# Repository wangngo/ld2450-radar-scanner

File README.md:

# ESP32-S3 + HLK-LD2450 24GHz mmWave Handheld Radar Scanner (with BMI160 Gyro Shake Compensation)

> **Handheld 24GHz mmWave multi-target human radar scanner** powered by **Hi-Link HLK-LD2450** (up to 3 simultaneous targets, 6m range, ±60° azimuth), **ESP32-S3-DevKitC-1 (N16R8)**, **Bosch BMI160 6-axis IMU** for handheld motion/shake compensation, and **on-board WS2812 RGB LED** proximity alerts.
>
> Features a zero-dependency **Wi-Fi SoftAP Web Radar UI** (`http://192.168.4.1` at ~11Hz live update), WebAudio distance-scaled Geiger beep, EMA trajectory smoothing, ghost-on-loss tracking, CSV data logging, **17 native C++ unit tests**, interactive HTML wiring/perfboard guides, and programmatic **KiCad 10 Schematic (`ERC 0`) & Carrier PCB (`DRC 0/0` + JLCPCB Gerbers)**.

---

## 1. Key Engineering Highlights

### A. Custom Stream-Safe `ld2450_parser` (Fixes 3 Bugs in Existing Libraries & Official Manual)

Why we wrote [`lib/ld2450_parser`](lib/ld2450_parser) instead of using popular Arduino libraries such as `RBEGamer/HLK-LD2450`:
1. **Fixes Out-of-Bounds (OOB) Memory Read:** Existing libraries check the frame footer at `rec_buf[i+28]` / `rec_buf[i+29]` without verifying `i + 29 < len`, causing out-of-bounds reads past the 256-byte receive buffer.
2. **Resilient to Split UART Frames at `256000` Baud:** Instead of relying on `Serial.readBytes()` with a 10ms timeout (which drops frames split across two reads), `Ld2450Parser` is a byte-by-byte streaming state machine that resynchronizes seamlessly on header (`AA FF 03 00`) and footer (`55 CC`).
3. **Correct Euclidean Distance vs. Distance-Gate Resolution (+ Official Manual Errata):**
   - Each 8-byte target record contains `(x_mm, y_mm, speed_cm_s, resolution_mm)`.
   - Existing libraries erroneously assign `target.distance = resolution`. In reality, the 4th field is the radar's *distance-gate resolution* (`320 mm`), while true distance is $\sqrt{x^2 + y^2}$ (`hypot(x_mm, y_mm)`).
   - **Official Manual Errata:** Hi-Link's `HLK-LD2450 Manual V1.00` (`docs/datasheets/HLK-LD2450-manual-V1.00.pdf`) contains an arithmetic typo in its worked example, writing `0x40 + 0x01*256 = 360 mm` when `0x0140` is actually **`320 mm`**.
4. **Boot-Time Multi-Target Configuration State Machine (`ld2450_cmd.h`):**
   - Automatically runs the Hi-Link binary command sequence on startup: `0x00FF` (Enable Config) → `0x0091` (Query Target Mode) → `0x0090` (Switch to Multi-Target if in Single mode) → `0x00FE` (End Config), with automatic retry if the radar stays silent in config mode.

### B. Handheld Motion & Shake Compensation (`lib/shake_detect` + Bosch `BMI160`)

Doppler 24GHz mmWave radars measure relative radial velocity. When a handheld scanner is tilted or panned by the operator's hand, stationary walls and objects appear as false moving targets, and the radar's rear lobe can pick up the operator behind the antenna:
- **Physical Shielding:** A metal backplate behind the LD2450 blocks rear-lobe reflections toward the operator (see cross-section in [`docs/wiring.html`](docs/wiring.html)).
- **100Hz Gyro Hysteresis Filter (`lib/shake_detect`):** Reads angular velocity magnitude $\|\omega\| = \sqrt{\omega_x^2 + \omega_y^2 + \omega_z^2}$ at 100Hz (`±250 °/s`) via the official Bosch Sensortec BMI160 driver (`lib/bmi160`, BSD-3-Clause).
  - Trips **ON** when $\|\omega\| \ge 30\text{ °/s}$, holds while $\ge 15\text{ °/s}$, and clears after **`300 ms`** of steady hold.
  - While shaking is detected, the Web UI dims radar targets and displays a shake warning banner, the CSV logger flags `shake=1`, and the on-board WS2812 RGB LED switches to dim blue instead of firing false proximity alerts.

### C. Hardware-as-Code: Programmatic KiCad 10 Schematic, PCB & Netlist-Verified Perfboard

All hardware design artifacts are generated and cross-checked deterministically via Python scripts in [`hardware/`](hardware):
- **`hardware/gen_schematic.py`** → [`hardware/carrier/carrier.kicad_sch`](hardware/carrier/carrier.kicad_sch) (**KiCad 10 ERC: 0 errors**) & [`carrier-schematic.pdf`](hardware/carrier/carrier-schematic.pdf).
- **`hardware/gen_carrier.py`** → [`hardware/carrier/carrier.kicad_pcb`](hardware/carrier/carrier.kicad_pcb) (66×66mm 2-layer Carrier PCB with top antenna notch, **KiCad 10 DRC: 0 violations, 0 unconnected**) & ready-to-order JLCPCB bundle [`carrier-gerber.zip`](hardware/carrier/carrier-gerber.zip).
- **`hardware/gen_perfboard.py`** → [`docs/perfboard.html`](docs/perfboard.html) (top & mirrored bottom soldering guide for a standard 7×9cm 24×30-hole perfboard, **automatically verified against the KiCad schematic netlist**).

---

## 2. Verified Pinout (`ESP32-S3-DevKitC-1 N16R8`)

> Interactive visual wiring diagram: open [`docs/wiring.html`](docs/wiring.html) and [`docs/perfboard.html`](docs/perfboard.html) in any browser.

| Peripheral | Module Pin | ESP32-S3 Pin | Notes & Hardware Gotchas |
| :--- | :--- | :--- | :--- |
| **HLK-LD2450** *(UART1 @ 256000)* | `5V` | `5V` | Requires **>200mA** at 5V (3.3V IO level). |
| | `GND` | `GND` | Common ground. |
| | `TX` | **`GPIO18`** *(RX1)* | Cross-over TX → RX. Avoid GPIO43/44 (used by onboard USB-UART0) and GPIO33–37 (used by Octal PSRAM on N16R8). |
| | `RX` | **`GPIO17`** *(TX1)* | Cross-over RX ← TX. |
| **Bosch BMI160** *(CJMCU-160, I2C @ 400kHz)* | `VIN` | `3V3` | Power from 3.3V rail. |
| | `GND` | `GND` | Common ground. |
| | `SDA` | **`GPIO8`** | I2C Data. |
| | `SCL` | **`GPIO9`** | I2C Clock. |
| | `CS` | **`3V3`** | **Must tie to `3V3`** to select I2C mode (`CS` low selects SPI). |
| | `SAO` *(SDO)* | **`GND`** | **Must tie to `GND`** for I2C address `0x68` (if left floating, module pull-up shifts address to `0x69`). |
| **On-Board RGB LED** | `WS2812` | **`GPIO48`** | Distance alert: Green (>4m) → Yellow → Flashing Red (faster as target approaches <4m); Dim Blue when shaking. |

---

## 3. Building, Testing & Flashing (PlatformIO)

### Run the 17 Native Unit Tests (No Hardware Required)
Tests cover `ld2450_parser` (datasheet frames, garbage resync, split frames, bad footer, 3-target decoding), `ld2450_cmd` / `ld2450_filter` (range gating, `y <= 0` behind-antenna rejection, optional `<1m` clustering), and `shake_detect` hysteresis:

```bash
pio test -e native
```

### Build & Flash Firmware (`s3_web`)
```bash
pio run -e s3_web -t upload
```
1. On your phone or laptop, connect to Wi-Fi AP **`LD2450-Radar`** (password: **`radar2450`**).
2. Open **`http://192.168.4.1`** in your browser.

### Hardware Bring-Up & Diagnostic Environments (`platformio.ini`)
- **`pio run -e s3_log -t upload`**: Identical to `s3_web` but with `ARDUINO_USB_CDC_ON_BOOT=0` so boot logs (`# radar cfg xong`, `# bmi160 chip 0xD1 ok`) output over the `CH340` UART0 USB port instead of the native USB CDC port.
- **`pio run -e i2cscan -t upload`**: Scans I2C bus on `GPIO8/9` and reads register `0x00` (`chip_id = 0xD1`) at `0x68` and `0x69` (`diag/i2cscan.cpp`).
- **`pio run -e led_test -t upload`**: Alternates `GPIO48` (Red) and `GPIO38` (Blue) to identify the on-board WS2812 pin across DevKitC-1 v1.0 / v1.1 revisions (`diag/led_test.cpp`).

---

## 4. Repository Structure

```text
├── src/
│   ├── main.cpp            # Firmware entry, Wi-Fi AP, HTTP endpoints (/data, /cfg), boot cfg FSM
│   ├── web_page.h          # Embedded HTML5 Canvas radar UI + WebAudio Geiger beep + CSV export
│   ├── imu.h               # Bosch BMI160 I2C wrapper (100Hz gyro -> shake_detect)
│   └── led.h               # WS2812 RGB LED distance & shake indicator
├── lib/
│   ├── ld2450_parser/      # Stream-safe LD2450 frame parser, Hi-Link command builder & target filters
│   ├── shake_detect/       # Gyro angular-velocity hysteresis detector
│   └── bmi160/             # Official Bosch Sensortec BMI160 driver (BSD-3-Clause)
├── test/                   # 17 native Unity unit tests (test_parser, test_cmd_filter, test_shake)
├── diag/                   # Hardware bring-up tools (i2cscan.cpp, led_test.cpp)
├── hardware/               # Python generators + KiCad 10 Schematic (ERC 0), PCB (DRC 0/0) & Gerbers
└── docs/                   # Interactive HTML wiring (wiring.html), 7x9cm perfboard guide (perfboard.html) & datasheet
```

---

## Tóm tắt Tiếng Việt

Dự án **Máy quét Radar cầm tay 24GHz mmWave (`HLK-LD2450` + `ESP32-S3-DevKitC-1 N16R8` + Gyro `Bosch BMI160` + LED RGB `WS2812`)**:
1. **Thư viện `lib/ld2450_parser` tự viết (17/17 test native PASS):** Sửa 3 lỗi của thư viện `RBEGamer/HLK-LD2450` (đọc tràn bộ nhớ OOB, mất gói UART bị cắt ở 256000 baud, gán nhầm độ phân giải 320mm thành khoảng cách `hypot(x,y)`) và đính chính lỗi cộng nhầm `360mm` vs `320mm` trong manual Hi-Link V1.00; tự động cấu hình chế độ multi-target (`0x00FF` → `0x0091` → `0x0090` → `0x00FE`) lúc khởi động.
2. **Chống nhiễu khi tay cầm rung (`BMI160` + `shake_detect`):** Đọc tốc độ góc gyro 100Hz, tự động làm mờ mục tiêu nhiễu trên giao diện Web (`http://192.168.4.1`) và báo LED xanh dương khi lia/lắc máy. Lưu ý phần cứng module CJMCU-160: phải nối **`CS → 3V3`** (chọn I2C) và **`SAO → GND`** (giữ địa chỉ `0x68`, nếu để hở chân `SAO` bị kéo lên `0x69`).
3. **Phần cứng & Mạch in:** Mở [`docs/wiring.html`](docs/wiring.html) và [`docs/perfboard.html`](docs/perfboard.html) để xem sơ đồ đấu nối trực quan và hướng dẫn hàn board đục lỗ 7×9cm (đã tự động đối chiếu netlist với KiCad 10 Schematic & Carrier PCB Gerber trong [`hardware/carrier/`](hardware/carrier)).

---

## License

MIT License (see [`LICENSE`](LICENSE)). `lib/bmi160/` is licensed under the BSD-3-Clause License by Bosch Sensortec.

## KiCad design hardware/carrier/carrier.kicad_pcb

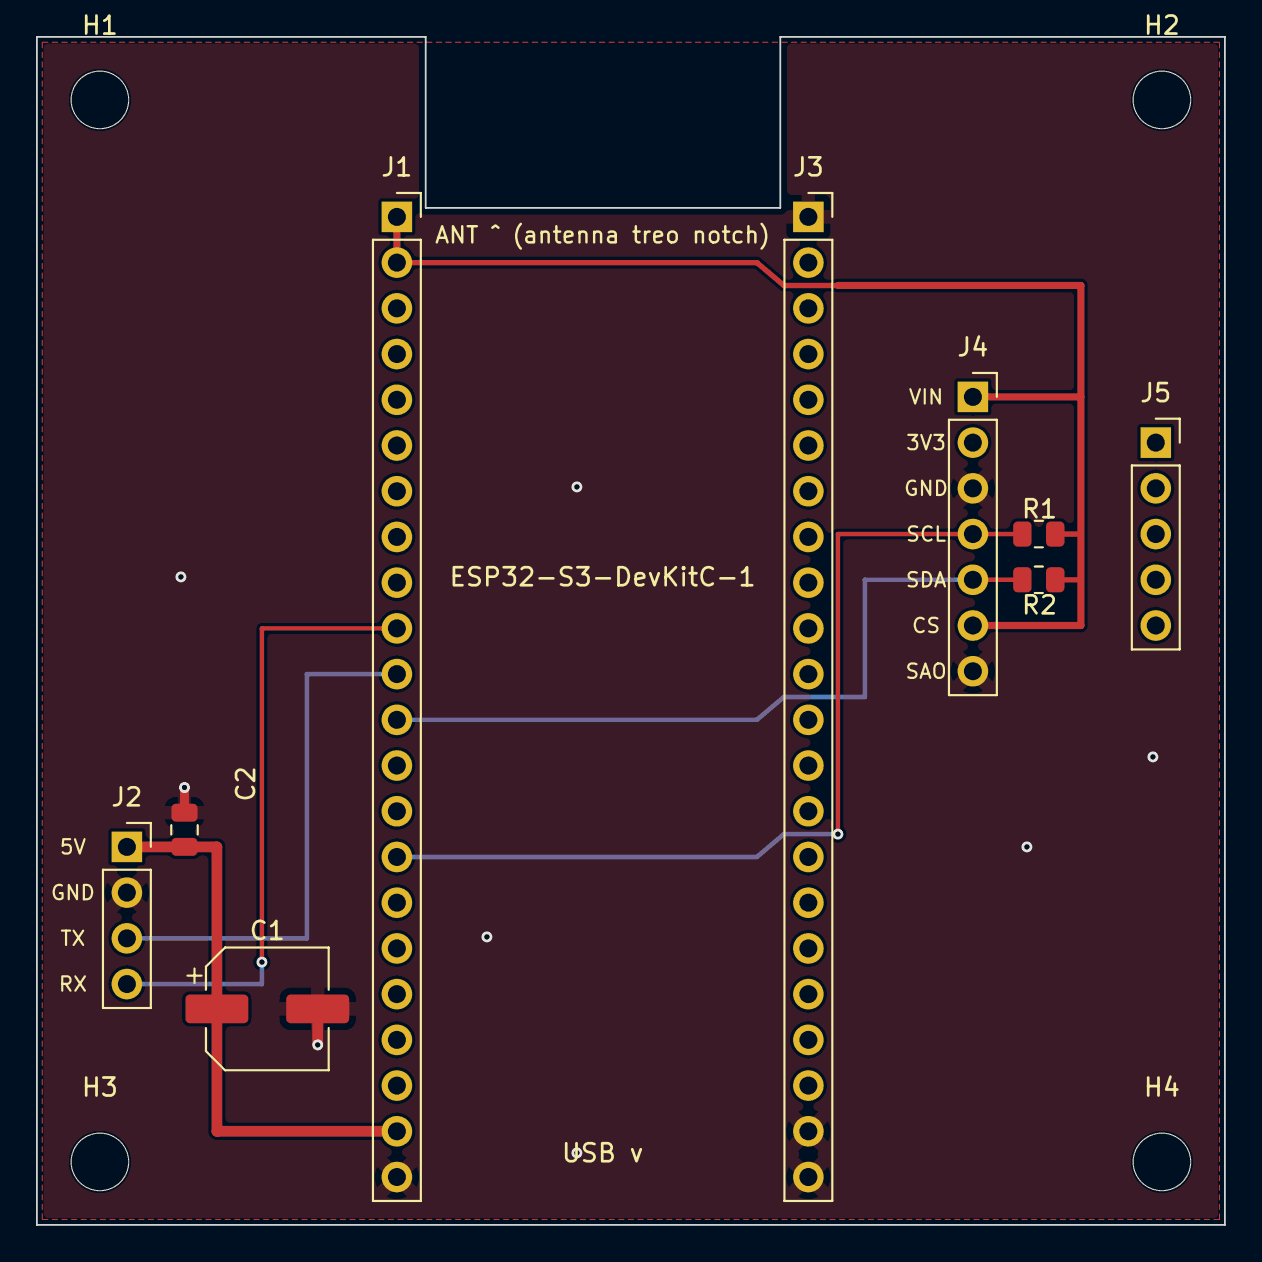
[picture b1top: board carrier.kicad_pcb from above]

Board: 2 copper layers, 66.0 x 66.0 mm, 13 parts (0 on the bottom side), 7 nets.

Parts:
C1: 100uF/10V; CP_Elec_6.3x5.4
C2: 100nF; C_0805_2012Metric
H1, H2, H3, H4: M3; MountingHole_3.2mm_M3
J1: DevKitC_J1; PinSocket_1x22_P2.54mm_Vertical
J2: LD2450; PinSocket_1x04_P2.54mm_Vertical
J3: DevKitC_J3; PinSocket_1x22_P2.54mm_Vertical
J4: BMI160_R; PinSocket_1x07_P2.54mm_Vertical
J5: BMI160_L; PinSocket_1x05_P2.54mm_Vertical
R1, R2: 4k7 DNP; R_0805_2012Metric

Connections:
+3V3: J1.1, J1.2, J4.1, J4.6, R1.2, R2.2
+5V: C1.1, C2.1, J1.21, J2.1
GND: C1.2, C2.2, J1.22, J2.2, J3.1, J3.21, J3.22, J4.3, J4.7
I2C_SCL: J1.15, J4.4, R1.1
I2C_SDA: J1.12, J4.5, R2.1
UART_RX: J1.11, J2.3
UART_TX: J1.10, J2.4

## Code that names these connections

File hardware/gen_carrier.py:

"""Sinh PCB carrier (ESP32-S3-DevKitC-1 + LD2450 + BMI160) bằng pcbnew của KiCad 10.

Chạy bằng Python đi kèm KiCad:
  /Applications/KiCad/KiCad.app/Contents/Frameworks/Python.framework/Versions/Current/bin/python3 hardware/gen_carrier.py
Netlist = docs/kicad-prep.md. Toạ độ mm, gốc góc trên-trái board, y hướng xuống.
Nguồn kích thước:
  - DevKitC-1 v1.1: DXF Espressif 20220429 -> pitch 2.54, J1 x=1.27 / J3 x=24.13 => row-to-row 22.86mm,
    chân 1 phía antenna, USB phía chân 22. Pinout J1/J3 theo user guide v1.1.
  - BMI160 CJMCU-160: 1x7 + 1x5, cách 10.16mm, hàng 5 lệch 1 bước (nằm giữa) — W xác nhận 2026-11-06.
  - LD2450: 1x4 5V/GND/Tx/Rx theo manual HLK V1.00 (chưa soi module thật).
"""
import os
import pcbnew

HERE = os.path.dirname(os.path.abspath(__file__))
OUT = os.path.join(HERE, "carrier", "carrier.kicad_pcb")
FPLIB = "/Applications/KiCad/KiCad.app/Contents/SharedSupport/footprints"
P = 2.54

B = pcbnew.BOARD()
mm = pcbnew.FromMM
V = lambda x, y: pcbnew.VECTOR2I(mm(x), mm(y))

ds = B.GetDesignSettings()
ds.m_TrackMinWidth = mm(0.2)
ds.m_ViasMinSize = mm(0.6)
ds.m_MinClearance = mm(0.2)

NETS = {}
def net(name):
    if name not in NETS:
        n = pcbnew.NETINFO_ITEM(B, name)
        B.Add(n)
        NETS[name] = n
    return NETS[name]

def fp(lib, name, ref, value, x, y, rot=0, pinnets=None):
    f = pcbnew.FootprintLoad(os.path.join(FPLIB, lib + ".pretty"), name)
    f.SetReference(ref)
    f.SetValue(value)
    f.SetPosition(V(x, y))
    if rot:
        f.SetOrientationDegrees(rot)
    B.Add(f)
    for pad in f.Pads():
        n = (pinnets or {}).get(pad.GetNumber())
        if n:
            pad.SetNet(net(n))
    return f

def pad_xy(f, num):
    p = [p for p in f.Pads() if p.GetNumber() == str(num)][0].GetPosition()
    return pcbnew.ToMM(p.x), pcbnew.ToMM(p.y)

def track(netname, pts, w, layer=pcbnew.F_Cu):
    for (x1, y1), (x2, y2) in zip(pts, pts[1:]):
        t = pcbnew.PCB_TRACK(B)
        t.SetStart(V(x1, y1)); t.SetEnd(V(x2, y2))
        t.SetWidth(mm(w)); t.SetLayer(layer); t.SetNet(net(netname))
        B.Add(t)

def via(netname, x, y):
    v = pcbnew.PCB_VIA(B)
    v.SetPosition(V(x, y)); v.SetDrill(mm(0.3)); v.SetWidth(mm(0.6))
    v.SetNet(net(netname))
    B.Add(v)

W, H = 66.0, 66.0
J1X, J3X, JY = 20.0, 20.0 + 22.86, 10.0          # DevKitC: chân 1 tại y=10
LDX, LDY = 5.0, 45.0                              # LD2450 chân 1 (5V)
BX, BY = 52.0, 20.0                               # BMI160 1x7 chân 1 (VIN)
jy = lambda n: JY + (n - 1) * P                   # y của chân n trên J1/J3

# --- footprint + gán net ---
J1 = fp("Connector_PinSocket_2.54mm", "PinSocket_1x22_P2.54mm_Vertical", "J1", "DevKitC_J1", J1X, JY,
        pinnets={"1": "+3V3", "2": "+3V3", "10": "UART_TX", "11": "UART_RX", "12": "I2C_SDA",
                 "15": "I2C_SCL", "21": "+5V", "22": "GND"})
J3 = fp("Connector_PinSocket_2.54mm", "PinSocket_1x22_P2.54mm_Vertical", "J3", "DevKitC_J3", J3X, JY,
        pinnets={"1": "GND", "21": "GND", "22": "GND"})
J2 = fp("Connector_PinSocket_2.54mm", "PinSocket_1x04_P2.54mm_Vertical", "J2", "LD2450", LDX, LDY,
        pinnets={"1": "+5V", "2": "GND", "3": "UART_RX", "4": "UART_TX"})   # 5V GND Tx Rx
J4 = fp("Connector_PinSocket_2.54mm", "PinSocket_1x07_P2.54mm_Vertical", "J4", "BMI160_R", BX, BY,
        pinnets={"1": "+3V3", "3": "GND", "4": "I2C_SCL", "5": "I2C_SDA", "6": "+3V3", "7": "GND"})
        # VIN 3V3 GND SCL SDA CS SAO ; chân 2 (3V3 ra của board BMI) để trống
J5 = fp("Connector_PinSocket_2.54mm", "PinSocket_1x05_P2.54mm_Vertical", "J5", "BMI160_L",
        BX + 10.16, BY + P)                        # OCS INT2 INT1 SCX SDX — NC

C1 = fp("Capacitor_SMD", "CP_Elec_6.3x5.4", "C1", "100uF/10V", 0, 0, pinnets={"1": "+5V", "2": "GND"})
C2 = fp("Capacitor_SMD", "C_0805_2012Metric", "C2", "100nF", 0, 0, rot=90, pinnets={"1": "+5V", "2": "GND"})
# đặt tụ sao cho pad1 (+) nằm đúng trên đường 5V
def place_pad1(f, x, y):
    px, py = pad_xy(f, 1)
    pos = f.GetPosition()
    f.SetPosition(V(pcbnew.ToMM(pos.x) + x - px, pcbnew.ToMM(pos.y) + y - py))
place_pad1(C2, 8.2, LDY)      # sát chân 5V LD2450
place_pad1(C1, 10.0, 54.0)
C2.Reference().SetPosition(V(11.6, 41.5))   # tránh silk J2

for i, (x, y) in enumerate([(3.5, 3.5), (W - 3.5, 3.5), (3.5, H - 3.5), (W - 3.5, H - 3.5)]):
    fp("MountingHole", "MountingHole_3.2mm_M3", f"H{i+1}", "M3", x, y)

# --- đi dây ---
F, Bk = pcbnew.F_Cu, pcbnew.B_Cu
ld = lambda n: LDY + (n - 1) * P
# 5V: J1.21 -> LD2450.1 (qua C1, C2)
track("+5V", [(J1X, jy(21)), (10, jy(21)), (10, LDY), (LDX, LDY)], 0.6, F)
c1g = pad_xy(C1, 2); via("GND", c1g[0], c1g[1] + 2.0); track("GND", [c1g, (c1g[0], c1g[1] + 2.0)], 0.6, F)
c2g = pad_xy(C2, 2); via("GND", c2g[0], c2g[1] - 1.4); track("GND", [c2g, (c2g[0], c2g[1] - 1.4)], 0.5, F)
# UART_RX (radar Tx -> GPIO18): toàn B.Cu
track("UART_RX", [(J1X, jy(11)), (15, jy(11)), (15, ld(3)), (LDX, ld(3))], 0.25, Bk)
# UART_TX (GPIO17 -> radar Rx): F.Cu rồi xuống B.Cu để vượt UART_RX
track("UART_TX", [(J1X, jy(10)), (12.5, jy(10)), (12.5, 51.4)], 0.25, F)
via("UART_TX", 12.5, 51.4)
track("UART_TX", [(12.5, 51.4), (12.5, ld(4)), (LDX, ld(4))], 0.25, Bk)
# 3V3: J1.2 -> dưới shield module, luồn giữa J3.2/J3.3 -> cột x=58 -> BMI VIN + CS
# (KHÔNG đi mép trên: antenna WROOM thò 6.3mm khỏi mép DevKitC, treo trên notch)
mid = lambda n: jy(n) + P / 2
X33 = 58.0
track("+3V3", [(J1X, jy(1)), (J1X, jy(2))], 0.4, F)
track("+3V3", [(J1X, jy(2)), (40.0, jy(2)), (41.5, mid(2)), (44.5, mid(2))], 0.3, F)
track("+3V3", [(44.5, mid(2)), (X33, mid(2)), (X33, BY + 5 * P), (BX, BY + 5 * P)], 0.4, F)
track("+3V3", [(X33, BY), (BX, BY)], 0.4, F)
# I2C pull-up 4k7 — DNP (lắp nếu CJMCU-160 không có pull-up sẵn)
for ref, pin, netname in (("R1", 4, "I2C_SCL"), ("R2", 5, "I2C_SDA")):
    y = BY + (pin - 1) * P
    r = fp("Resistor_SMD", "R_0805_2012Metric", ref, "4k7 DNP", 0, 0, pinnets={"1": netname, "2": "+3V3"})
    place_pad1(r, 54.75, y)
    try:
        r.SetDNP(True)
    except AttributeError:
        pass
    r.Reference().SetPosition(V(55.7, y - 1.4 if pin == 4 else y + 1.4))
    track(netname, [(BX, y), (54.75, y)], 0.25, F)
    track("+3V3", [pad_xy(r, 2), (X33, y)], 0.3, F)
track("I2C_SDA", [(J1X, jy(12)), (40.0, jy(12)), (41.5, mid(11)), (46.0, mid(11)), (46.0, BY + 4 * P), (BX, BY + 4 * P)], 0.25, Bk)
track("I2C_SCL", [(J1X, jy(15)), (40.0, jy(15)), (41.5, mid(14)), (44.5, mid(14))], 0.25, Bk)
via("I2C_SCL", 44.5, mid(14))
track("I2C_SCL", [(44.5, mid(14)), (44.5, BY + 3 * P), (BX, BY + 3 * P)], 0.25, F)
# GND của BMI (chân 3, SAO chân 7) nối qua pour cả 2 lớp; thêm via khâu
for x, y in [(30, 62), (8, 30), (30, 25), (55, 45), (62, 40), (25, 50)]:
    via("GND", x, y)

# --- viền board ---
# notch mép trên cho antenna WROOM (DXF: module x3.75..21.75 vượt mép board tới y69.15
# -> carrier x~22.5..40.5, y~2.2..8.8): antenna treo trên khoảng trống, không đồng bên dưới
NX0, NX1, NY = J1X + 1.6, J3X - 1.56, 9.5
pts = [(0, 0), (NX0, 0), (NX0, NY), (NX1, NY), (NX1, 0), (W, 0), (W, H), (0, H), (0, 0)]
for (x1, y1), (x2, y2) in zip(pts, pts[1:]):
    s = pcbnew.PCB_SHAPE(B); s.SetShape(pcbnew.SHAPE_T_SEGMENT)
    s.SetStart(V(x1, y1)); s.SetEnd(V(x2, y2)); s.SetLayer(pcbnew.Edge_Cuts); s.SetWidth(mm(0.1))
    B.Add(s)

def poly(x0, y0, x1, y1):
    c = pcbnew.SHAPE_LINE_CHAIN()
    for x, y in [(x0, y0), (x1, y0), (x1, y1), (x0, y1)]:
        c.Append(mm(x), mm(y))
    c.SetClosed(True)
    return c

# --- GND pour 2 lớp ---
for layer in (F, Bk):
    z = pcbnew.ZONE(B); z.SetLayer(layer); z.SetNet(net("GND"))
    z.Outline().AddOutline(poly(0.3, 0.3, W - 0.3, H - 0.3))
    z.SetLocalClearance(mm(0.3)); z.SetMinThickness(mm(0.25))
    B.Add(z)
# --- silk: tên chân + hướng cắm (socket đối xứng, cắm ngược 180° là cháy) ---
def silk(txt, x, y, size=0.8, rot=0, layer=pcbnew.F_SilkS):
    t = pcbnew.PCB_TEXT(B); t.SetText(txt); t.SetPosition(V(x, y)); t.SetLayer(layer)
    if layer == pcbnew.B_SilkS:
        t.SetMirrored(True)
    t.SetTextSize(V(size, size)); t.SetTextThickness(mm(size * 0.15))
    if rot:
        t.SetTextAngleDegrees(rot)
    B.Add(t)
for i, n in enumerate(["5V", "GND", "TX", "RX"]):
    silk(n, 2.0, ld(i + 1))
for i, n in enumerate(["VIN", "3V3", "GND", "SCL", "SDA", "CS", "SAO"]):
    silk(n, 49.4, BY + i * P)
silk("ANT ^ (antenna treo notch)", (J1X + J3X) / 2, NY + 1.5, 0.9)
silk("ESP32-S3-DevKitC-1", (J1X + J3X) / 2, 30.0, 1.0)
silk("USB v", (J1X + J3X) / 2, 62.0, 1.0)
silk("ld2450-radar-scanner carrier v1", (J1X + J3X) / 2, 40.0, 0.8, layer=pcbnew.B_SilkS)

pcbnew.ZONE_FILLER(B).Fill(B.Zones())
os.makedirs(os.path.dirname(OUT), exist_ok=True)
B.Save(OUT)
print("saved", OUT)
